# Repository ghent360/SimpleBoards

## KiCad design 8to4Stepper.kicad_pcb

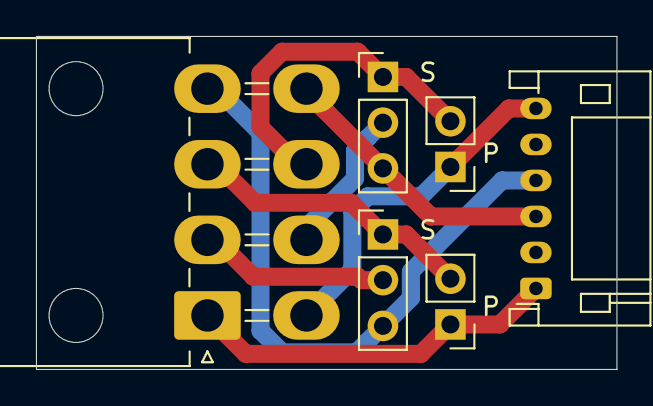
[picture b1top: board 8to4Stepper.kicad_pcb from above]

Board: 2 copper layers, 32.2 x 18.5 mm, 6 parts (0 on the bottom side), 8 nets.

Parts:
J1: Out; JST_PH_S6B-PH-K_1x06_P2.00mm_Horizontal
J2: In; Molex_Mini-Fit_Jr_5569-08A2_2x04_P4.20mm_Horizontal
JP1: W1a; PinHeader_1x03_P2.54mm_Vertical
JP2: W2a; PinHeader_1x03_P2.54mm_Vertical
JP3: W1b; PinHeader_1x02_P2.54mm_Vertical
JP4: W2b; PinHeader_1x02_P2.54mm_Vertical

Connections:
/BLK: J1.1, J2.1, JP3.1
/BLU: J2.7, JP2.1, JP4.2
/BRN: J2.3, JP1.1, JP3.2
/ORG: J1.4, J2.4, JP1.3
/PUR: J2.6, JP2.2
/RED: J1.6, J2.5, JP4.1
/WHT: J2.2, JP1.2
/YEL: J1.3, J2.8, JP2.3
